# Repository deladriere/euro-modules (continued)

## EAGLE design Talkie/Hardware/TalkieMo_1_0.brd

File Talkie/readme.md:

Arduino based Talkie Eurorack Module 
Have your modular speak out the CV
This arduino based module works thanks to a clever library : Talkie from https://github.com/going-digital/Talkie 

Jean-Luc Deladrière, Hanabi SPRL 2006-2014. Except where otherwise noted, content on this site is licensed under a cc-by-sa 3.0 license.

Numbers 

#Functions
##Bank
For the moment I have added 4 sound banks :
0:digits (from 0 to 9) male voice
1:digits (from 0 to 9) female voice
2:big numbers (from 0 to 9999999)
3:voltmeter (reading the CV voltage)
4:frequencemeter (just saying "Hertz" instead of "Volts")
5:Spell the alphabet
6:nato alphabet

I plan to add a 7th bank with a large vocabulary and a 8th bank with weird sounds
random mode

##CV

CV signal change the words or phrase to be said

##Gate

Pressing the button start the complete sound in trigger mode. (regardless of it's length) 
If the trigger switch is off, the gate will start the sound and hold it as long as the gate level stays up. Very useful to create crazy rhythms.

If the cable is plugged in, the gate is triggered via an external signal

##Trigger

Choose between trigger mode or gated mode

##Bend

If bend is on, the bend pot ... distords the sound.

##Speed

Change the speed

##Pitch

Change the pitch

## Todo.todo
* publish schematic
* publish pcb
* add picture of panel & pcb
* merge library in main code 
* add R/shottky in  with entries for protection @done(2014-11-30)
* add mousers ref to each part (mouser cart : link)
* Add female voice

more info here : http://elek101.blogspot.be/2014/10/talkie-eurorack-module-part-1-concept.html

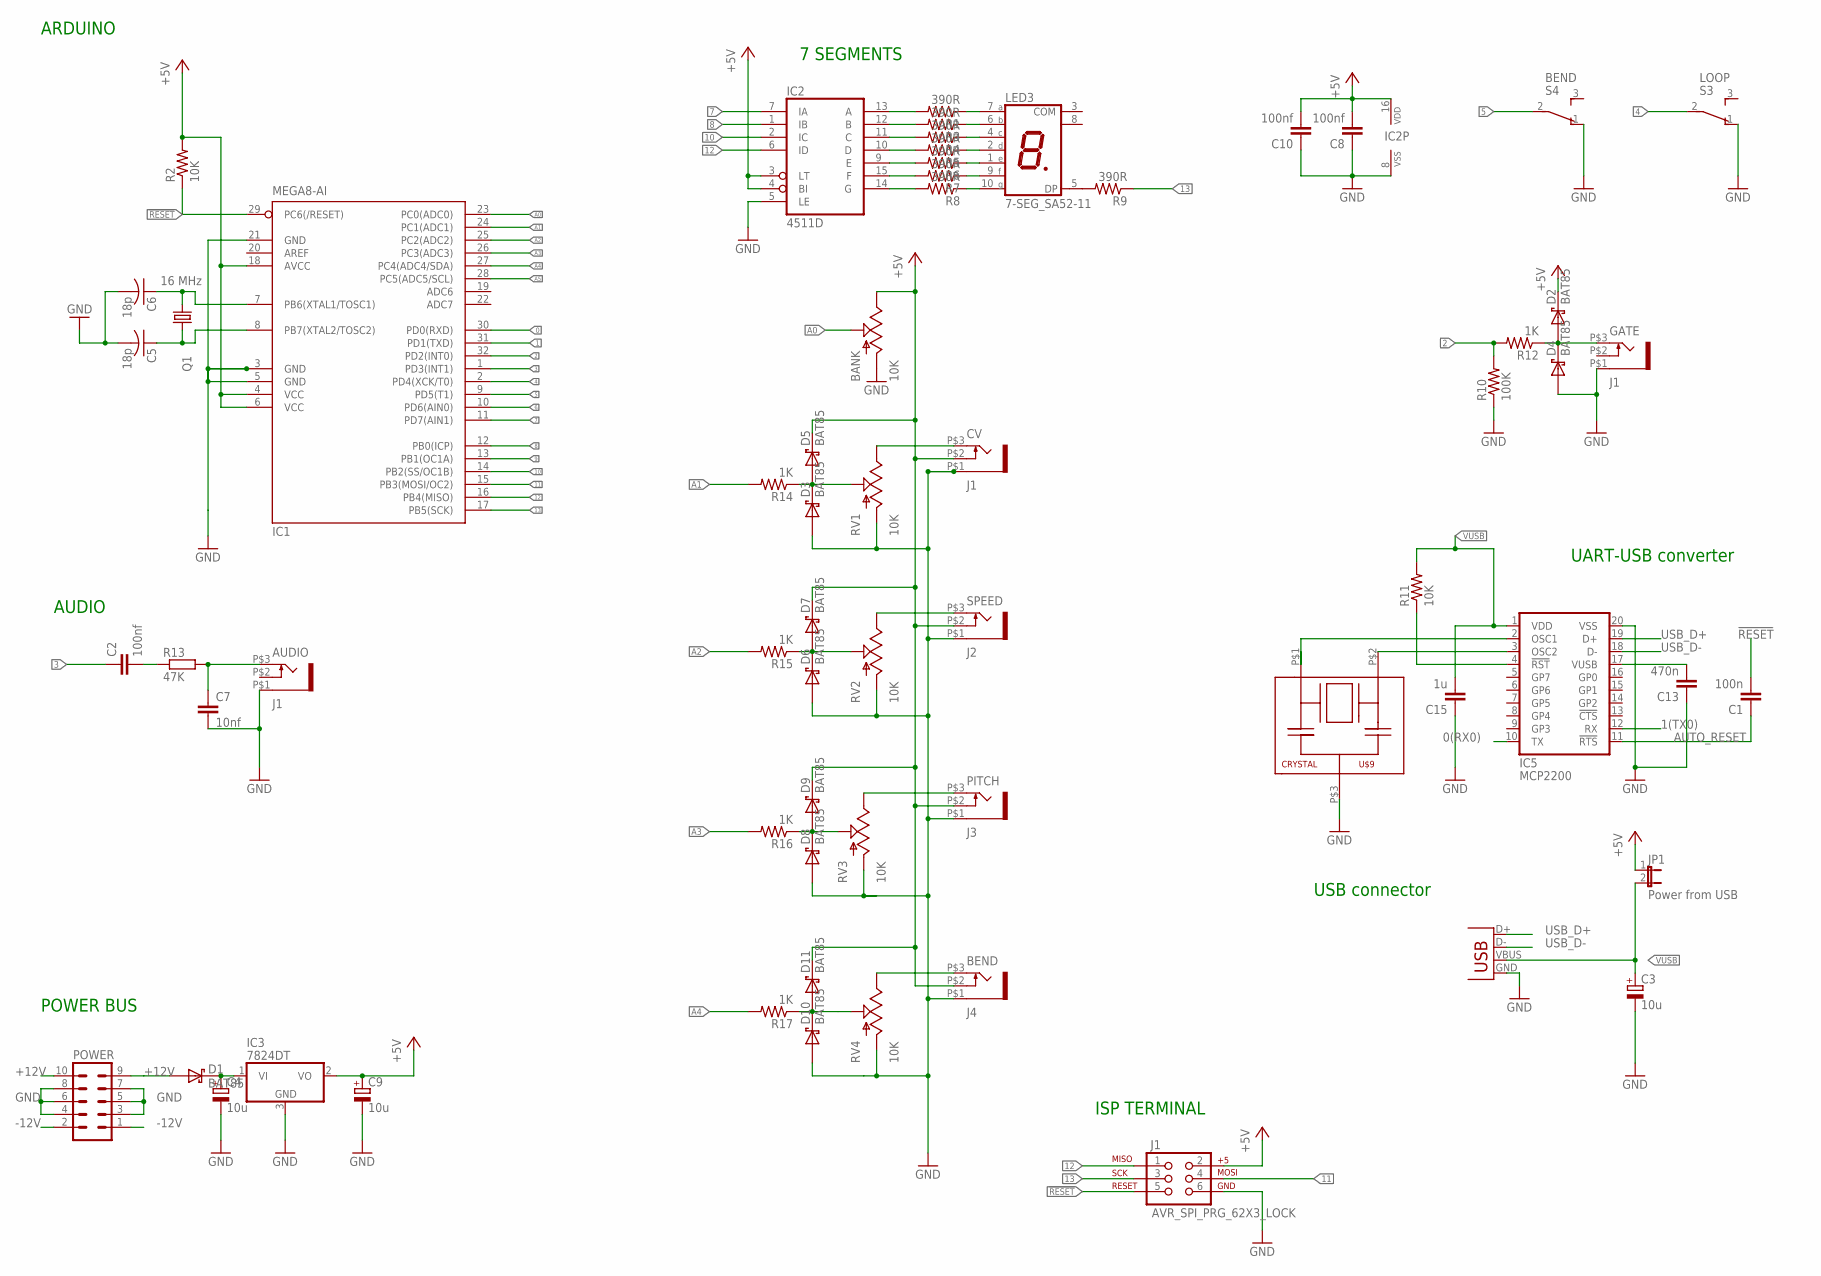
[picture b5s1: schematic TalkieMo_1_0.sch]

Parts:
AUDIO: J1; THONKICONN
BANK: 10K; ALPS_POT
BEND: J4; THONKICONN
C1: 100n; 0805
C2, C8, C10: 100nf; C0805
C3, C4, C9: 10u; R/2012-12R
C5, C6: 18p; C0805K
C7: 10nf; C0805
C13: 470n; 0805
C15: 1u; 0805
CV: J1; THONKICONN
D1, D2, D3, D4, D5, D6, D7, D8, D9, D10, D11: BAT85; SMA-DIODE
GATE: J1; THONKICONN
IC1: MEGA8-AI; TQFP32-08
IC2: 4511D; SO16
IC3: 7824DT; TO252
IC5: MCP2200; SO20
J1: AVR_SPI_PRG_62X3_LOCK; 2X3_LOCK
JP1: Power from USB; JP1
LED3: 7-SEG_SA52-11; SA52-11
PITCH: J3; THONKICONN
POWER: 10_PIN_HEADER; MA05-2
Q1: 16 MHz; CTS406
R1, R3, R4, R5, R6, R7, R8, R9: 390R; M0805
R2, R11: 10K; M0805
R10: 100K; M0805
R12, R14, R15, R16, R17: 1K; M0805
R13: 47K; M0805
RV1, RV2, RV3, RV4: 10K; ALPS_POT
S3: LOOP; TL3XPO
S4: BEND; TL3XPO
SPEED: J2; THONKICONN
U$9: CRYSTAL
X3: USB; USB-B-PTH-VERTICAL

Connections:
0: IC1.30 (PD0(RXD))
0(RX0): IC5.10 (TX)
1: IC1.31 (PD1(TXD))
1(TX0): IC5.12 (RX)
2: IC1.32 (PD2(INT0)), R10.2, R12.2
3: C2.1, IC1.1 (PD3(INT1))
4: IC1.2 (PD4(XCK/T0)), S3.2
5: IC1.9 (PD5(T1)), S4.2
6: IC1.10 (PD6(AIN0))
7: IC1.11 (PD7(AIN1)), IC2.7 (IA)
8: IC1.12 (PB0(ICP)), IC2.1 (IB)
9: IC1.13 (PB1(OC1A))
10: IC1.14 (PB2(SS/OC1B)), IC2.2 (IC)
11: IC1.15 (PB3(MOSI/OC2)), J1.4
12: IC1.16 (PB4(MISO)), IC2.6 (ID), J1.1
13: IC1.17 (PB5(SCK)), J1.3, R9.1
!RESET: C1.2, IC1.29 (PC6(/RESET)), J1.5, R2.1
+5V: BANK.P$1 (E), BEND.P$2 (4), C8.2, C9.+, C10.2, CV.P$2 (4), D2.C, D5.C, D7.C, D9.C, D11.C, IC1.4 (VCC), IC1.6 (VCC), IC1.18 (AVCC), IC2.3 (LT), IC2.4 (BI), IC2.16 (VDD), IC3.2 (VO), J1.2, JP1.1, PITCH.P$2 (4), R2.2, SPEED.P$2 (4)
+12V: D1.A, POWER.9, POWER.10
-12V: POWER.1, POWER.2
A0: BANK.P$2 (S), IC1.23 (PC0(ADC0))
A1: IC1.24 (PC1(ADC1)), R14.2
A2: IC1.25 (PC2(ADC2)), R15.2
A3: IC1.26 (PC3(ADC3)), R16.2
A4: IC1.27 (PC4(ADC4/SDA)), R17.2
A5: IC1.28 (PC5(ADC5/SCL))
AUTO_RESET: C1.1, IC5.11 (!RTS)
GND: AUDIO.P$1 (5), BANK.P$3 (A), BEND.P$1 (5), C4.-, C5.2, C6.2, C7.2, C8.1, C9.-, C10.1, C13.1, C15.1, CV.P$1 (5), D3.A, D4.A, D6.A, D8.A, D10.A, GATE.P$1 (5), IC1.3 (GND), IC1.5 (GND), IC1.21 (GND), IC2.5 (LE), IC2.8 (VSS), IC3.3 (GND), IC5.20 (VSS), J1.6, PITCH.P$1 (5), POWER.3, POWER.4, POWER.5, POWER.6, POWER.7, POWER.8, R10.1, RV1.P$3 (A), RV2.P$3 (A), RV3.P$3 (A), RV4.P$3 (A), S3.1 (O), S4.1 (O), SPEED.P$1 (5), U$9.P$3 (3), X3.GND
unnamed: CV.P$3 (3), RV1.P$1 (E)
unnamed: C5.1, IC1.8 (PB7(XTAL2/TOSC2)), Q1.1
unnamed: LED3.5 (DP), R9.2
unnamed: RV2.P$1 (E), SPEED.P$3 (3)
unnamed: C4.+, D1.C, IC3.1 (VI)
unnamed: PITCH.P$3 (3), RV3.P$1 (E)
unnamed: IC2.13 (A), R1.2
unnamed: D3.C, D5.A, R14.1, RV1.P$2 (S)
unnamed: LED3.7 (A), R1.1
unnamed: IC5.3 (OSC2), U$9.P$2 (2)
unnamed: C6.1, IC1.7 (PB6(XTAL1/TOSC1)), Q1.3 (2)
unnamed: AUDIO.P$3 (3), C7.1, R13.2
unnamed: C2.2, R13.1
unnamed: IC2.12 (B), R3.2
unnamed: LED3.6 (B), R3.1
unnamed: IC2.11 (C), R4.2
unnamed: LED3.4 (C), R4.1
unnamed: IC2.10 (D), R5.2
unnamed: LED3.2 (D), R5.1
unnamed: IC2.9 (E), R6.2
unnamed: LED3.1 (E), R6.1
unnamed: IC2.15 (F), R7.2
unnamed: LED3.9 (F), R7.1
unnamed: IC2.14 (G), R8.2
unnamed: LED3.10 (G), R8.1
unnamed: IC5.2 (OSC1), U$9.P$1 (1)
unnamed: IC5.4 (!RST), R11.1
unnamed: C13.2, IC5.17 (VUSB)
unnamed: D2.A, D4.C, GATE.P$3 (3), R12.1
unnamed: D6.C, D7.A, R15.1, RV2.P$2 (S)
unnamed: D8.C, D9.A, R16.1, RV3.P$2 (S)
unnamed: BEND.P$3 (3), RV4.P$1 (E)
unnamed: D10.C, D11.A, R17.1, RV4.P$2 (S)
USB_D+: IC5.19 (D+), X3.D+
USB_D-: IC5.18 (D-), X3.D-
VUSB: C3.+, C15.2, IC5.1 (VDD), JP1.2, R11.2, X3.VBUS

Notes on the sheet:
7 SEGMENTS
UART-USB converter
USB connector
ISP TERMINAL
POWER BUS
ARDUINO
AUDIO

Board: 2 copper layers, 64 parts (5 on the bottom side), 57 nets, no tracks yet.

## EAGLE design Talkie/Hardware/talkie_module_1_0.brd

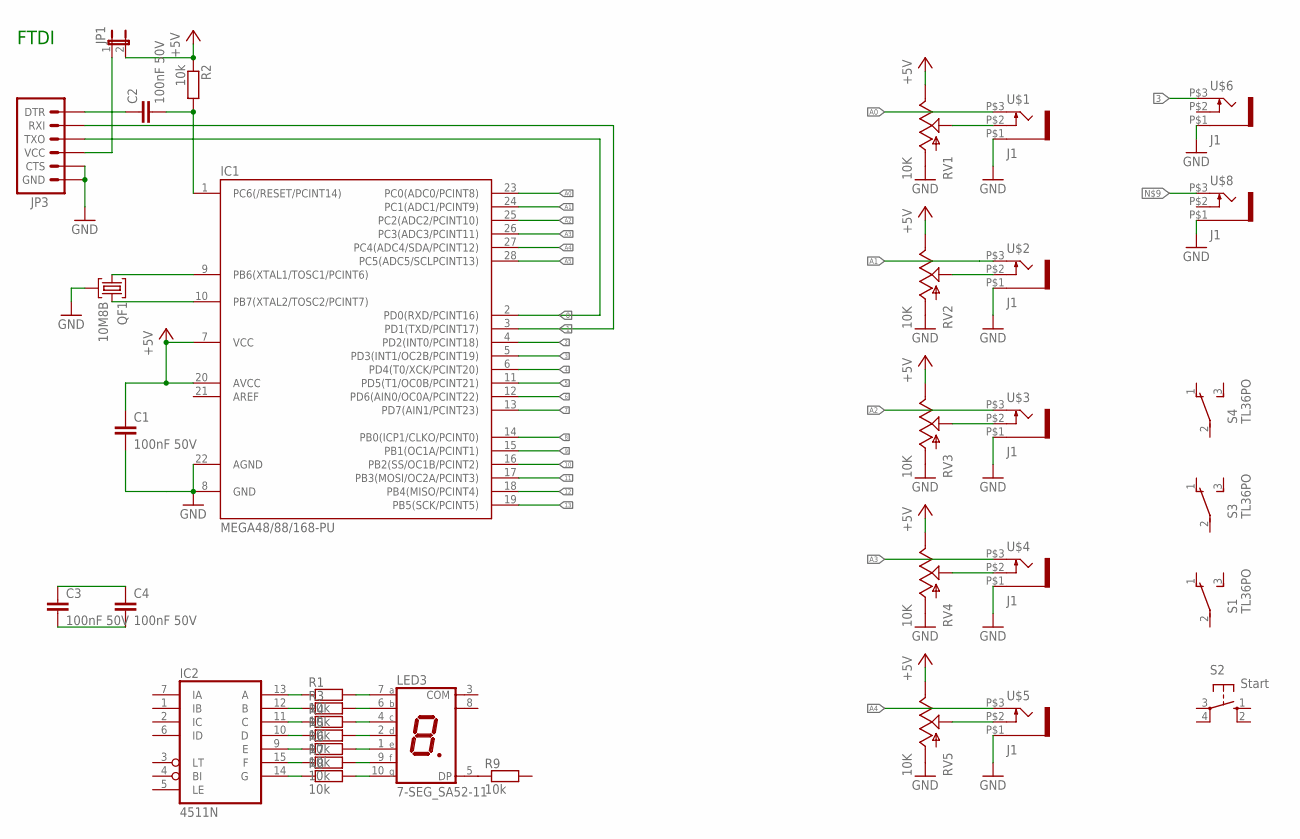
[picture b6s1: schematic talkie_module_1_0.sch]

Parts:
C1, C2, C3, C4: 100nF 50V; C025-025X050
IC1: MEGA48/88/168-PU; DIL28-3
IC2: 4511N; DIL16
JP1: JP1E; JP1
JP3: ARDUINO_SERIAL_PROGRAMLOCK; 1X06_LOCK
LED3: 7-SEG_SA52-11; SA52-11
QF1: 10M8B; HC49U
R1, R2, R3, R4, R5, R6, R7, R8, R9: 10k; RES-AXIAL-0.4
RV1, RV2, RV3, RV4, RV5: 10K; ALPS_POT
S1, S3, S4: TL36PO; TL3XPO
S2: Start; B3F-10XX
U$1, U$2, U$3, U$4, U$5, U$6, U$8: J1; THONKICONN

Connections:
0: IC1.2 (PD0(RXD/PCINT16)), JP3.3 (TXO)
1: IC1.3 (PD1(TXD/PCINT17)), JP3.2 (RXI)
2: IC1.4 (PD2(INT0/PCINT18))
3: IC1.5 (PD3(INT1/OC2B/PCINT19)), U$6.P$3 (3)
4: IC1.6 (PD4(T0/XCK/PCINT20))
5: IC1.11 (PD5(T1/OC0B/PCINT21))
6: IC1.12 (PD6(AIN0/OC0A/PCINT22))
7: IC1.13 (PD7(AIN1/PCINT23))
8: IC1.14 (PB0(ICP1/CLKO/PCINT0))
9: IC1.15 (PB1(OC1A/PCINT1))
10: IC1.16 (PB2(SS/OC1B/PCINT2))
11: IC1.17 (PB3(MOSI/OC2A/PCINT3))
12: IC1.18 (PB4(MISO/PCINT4))
13: IC1.19 (PB5(SCK/PCINT5))
+5V: C1.1, IC1.7 (VCC), IC1.20 (AVCC), JP1.2, R2.P$1 (1), RV1.P$1 (E), RV2.P$1 (E), RV3.P$1 (E), RV4.P$1 (E), RV5.P$1 (E)
A0: IC1.23 (PC0(ADC0/PCINT8)), U$1.P$3 (3)
A1: IC1.24 (PC1(ADC1/PCINT9)), U$2.P$3 (3)
A2: IC1.25 (PC2(ADC2/PCINT10)), U$3.P$3 (3)
A3: IC1.26 (PC3(ADC3/PCINT11)), U$4.P$3 (3)
A4: IC1.27 (PC4(ADC4/SDA/PCINT12)), U$5.P$3 (3)
A5: IC1.28 (PC5(ADC5/SCLPCINT13))
GND: C1.2, IC1.8 (GND), IC1.22 (AGND), JP3.5 (CTS), JP3.6 (GND), QF1.2, RV1.P$3 (A), RV2.P$3 (A), RV3.P$3 (A), RV4.P$3 (A), RV5.P$3 (A), U$1.P$1 (5), U$2.P$1 (5), U$3.P$1 (5), U$4.P$1 (5), U$5.P$1 (5), U$6.P$1 (5), U$8.P$1 (5)
unnamed: RV1.P$2 (S), U$1.P$2 (4)
unnamed: RV2.P$2 (S), U$2.P$2 (4)
unnamed: IC1.9 (PB6(XTAL1/TOSC1/PCINT6)), QF1.1
unnamed: JP1.1, JP3.4 (VCC)
unnamed: RV3.P$2 (S), U$3.P$2 (4)
unnamed: RV4.P$2 (S), U$4.P$2 (4)
unnamed: RV5.P$2 (S), U$5.P$2 (4)
unnamed: IC2.13 (A), R1.P$1 (1)
unnamed: LED3.7 (A), R1.P$2 (2)
unnamed: LED3.5 (DP), R9.P$1 (1)
unnamed: IC1.10 (PB7(XTAL2/TOSC2/PCINT7)), QF1.3
unnamed: C2.2, IC1.1 (PC6(/RESET/PCINT14)), R2.P$2 (2)
unnamed: C2.1, JP3.1 (DTR)
unnamed: IC2.12 (B), R3.P$1 (1)
unnamed: LED3.6 (B), R3.P$2 (2)
unnamed: IC2.11 (C), R4.P$1 (1)
unnamed: LED3.4 (C), R4.P$2 (2)
unnamed: IC2.10 (D), R5.P$1 (1)
unnamed: LED3.2 (D), R5.P$2 (2)
unnamed: IC2.9 (E), R6.P$1 (1)
unnamed: LED3.1 (E), R6.P$2 (2)
unnamed: IC2.15 (F), R7.P$1 (1)
unnamed: LED3.9 (F), R7.P$2 (2)
unnamed: IC2.14 (G), R8.P$1 (1)
unnamed: LED3.10 (G), R8.P$2 (2)
unnamed: C3.1, C4.1
unnamed: C3.2, C4.2
VDD: IC2.16 (VDD)
VSS: IC2.8 (VSS)

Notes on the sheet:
FTDI

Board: 2 copper layers, 35 parts (0 on the bottom side), 37 nets, no tracks yet.

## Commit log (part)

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2014-09-03 first push
2014-09-03 little update
2014-09-03 test commit
2014-09-10 pitch bending
2014-10-08 pour sauver le nouveau pcb
2014-10-08 modified readme
2014-10-08 .gitignore is now working
2014-10-08 ready to broadcast on my blog
2014-10-12 removed a redundant wait in talkie2.cpp moved definition in talkie2.h to share them across the script and talkie2.cpp change pot mapping for alphabet
2014-11-08 Explaining the little update to the original script to match the hardware
2014-11-29 MozMo opening Version 1_1 / Adding software folder
2014-12-12 Mozmo software update Talkie added female voice Talkie rename pcb
2014-12-30 Talkie renamed to Talko Talko Schematic Added female voice
2014-12-30 updating Talko readme
2015-01-03 adding schematic image file to Talko
2015-01-17 renaming mozzi folder to mozmo
2015-01-20 Fixing a bug in loop mode changing switch reference @ Mouser (for a bigger lever)
2015-01-28 Adding jumper picture to Mozmo Adding vocabulary to Talko Adding Counter mode to Talko Use dot led for mode > 10
2015-01-28 Changing Mozmo Jumper picture to png
2015-02-27 adding turing machine script to Mozmo
2015-03-08 Adding a LFO for MozMo
2015-03-18 Minor changes to MozMo's LFO
2015-03-18 Adding noise color option to noise generator
2015-03-19 changing Mozmo image in readme
2015-03-25 First Raspo commit : eagle schematic & numbers radio simulator
2015-03-25 adding talko images
2015-03-25 adding Talko pcb image
2015-03-29 Adding pcb image error 1
2015-03-29 Adding error on Talko's pcb
2015-03-29 Posting Talko's panel (still drafted)
2015-04-13 Updating Mozmo readme
2015-04-17 adding link to Mozmo's install page
2015-04-17 update Talko's readme
2015-05-27 Adding a basic setup schematic
2015-05-27 Updated basic drawing
2015-05-29 Updated pcb to version 1.1 Updated Readme to explain changes
2015-07-08 renaming Talko pots on v1.1
2015-07-18 Adding panel to Talko New version of Talko_1 : added 60 words and random words mode
2015-07-19 Adding Talko panel image
2015-07-29 Update Talko pot Pitch & Speed position Added more words to vocabulary (now has 60)
2015-07-29 Uploading Talko assembly pictures
2015-07-29 Resize Talko panel image
2015-07-31 Talko readme update
2015-08-07 removing morse
2015-08-07 Updating Talko's readme
2015-08-08 Fixing Talko code under Arduino 1.6.x Adding link to Talko uploading code
2015-08-26 adding Bank # 12 : DSC sentences
2015-09-19 Uploading Cantarino example for Talko
2015-09-22 Adding Canto script to Talko
2015-09-27 Uploading Talko_QC
2015-09-27 Talko switch back to low = active
2015-10-07 Various updates on Mozmo & Talko
2015-10-07 Canto new version : Gate trigger : vowel holds while gate is on - use duty cycle of gate to give rhythm (I use my LFO2 from Pittsburg Modular for that) Sound : choose between 19 different vowels soun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
2015-10-07 Updating Readme because it works fine on all OS
2015-10-11 Taco's Canto has now pitch bend and sound change while note one
2015-12-04 Talko : updating bending intensity to a stronger effect Adding interupt to change bank when gate is rising Moving Readme to http://www.polaxis.be/talko/
2015-12-13 Talk update : reverse speech/loop switch position : lever down for loop mode
2015-12-26 Talko : made some room to prepare for French digit / Talko_QC added interrupt change to blink LED 13 on gate
2015-12-28 Talk : Adding a new sentence coded with QBoxPro
2016-01-08 renaming Talko_1 to Talko + adding a zip to hold these 3 files :-)
2016-01-15 Pushing TalkoVCO for the first time
2016-02-05 TalkoVCO testing "mouth drum"
2016-03-04 Talk new version of VCO : includes now a "Throat Beat Box" mode
2016-03-24 VCO mode : adding 2 new words "Error" "Instruments"
2016-03-24 Adding TalkoVCO Zip file
2016-04-13 Adding code for Talko 1.2
2016-04-27 Talk 1.2 includes VCO mode
2016-05-18 adding images to talko manual
2016-05-18 Adding picture to Talko 1.2 assembly manual
2016-05-18 Adding images to Talko 1.2 Assembly Manual
2016-05-18 Updating image
2016-07-27 Adding some Grains code to talko
2016-07-27 Delete .DS_Store
    deletion od .ds_store
2016-08-23 Talko : Changed #include<Time.h> into #include<Timelib.h> (compilation issues)
2016-11-16 Adding Aques click board
2016-11-23 adding SAMD21 code
2016-11-23 Kaija vox : main functions working
2016-11-23 Emy first commit
2016-11-25 minor update on Emy ! hang on exit from SD tts
2016-11-30 Adding Hataken’s timer
2016-11-30 Correction on vocal countdown for Hataken’s timer
2016-11-30 Adding code to Emy platform
2016-11-30 Kaiwa dirty fixing Interrupt trigger when using rotary even if if interrupt is detached !!!
2016-12-14 Hataken’s timer : connected to Processing
2016-12-14 Kaiwa now connected to Kaiwa VOX and speaking
2016-12-17 Kawai : removing interrupt triggering of voice + extended I2C message to 50 bytes (instead of 32 !)
2016-12-17 kaiwa : testing priority to gate (not very fast :-( )
2016-12-18 Updating Talko Hardware with version 1.2 (sorry I should have done that long time ago)
2016-12-21 Adding switches in emy QC
2016-12-21 Kaiwa sending the correct String lenght to synth
2016-12-21 various trivial changes
2016-12-31 Kaiwa speaks from SD
2017-01-06 Kaiwa : display SD error + voice parameter while SD card reading
2017-01-11 Adding Talko1.2 midi
2017-01-11 Talko midi : need to read midi while looping in vco . will this work ? ….
2017-01-11 Kaiwa : get correct line when gate goes high
2017-01-20 adding Talko Print notes
2017-01-21 Mea Vox first commit
2017-01-21 Kaiwa Vox first commit
2017-01-30 Mea_Vox_Arduino simplify connections
2017-02-01 trying to install my own board management
2017-02-01 Testing custom board management
2017-02-03 Kaiwa : first test for long vowels
2017-02-15 Kaiwa : master clock hack while sd tts
2017-02-18 Updates to Talko Readme
2017-02-22 Talko VCO mode uses 1V/octave tracking to play notes.
2017-03-01 Kaiwa : move master pitch function in main menu
2017-03-04 Talko Box : new iteration
2017-03-04 Talko Box : addling Minitel connector
2017-03-04 Talko Box : full with midi connector
2017-03-08 Emy : testing Adafruit library
2017-03-22 Kaiwa : long press to get out from master clock & short press to change pitch
2017-03-22 Emy: the story begin
2017-03-22 Talko : small tweak to 3D box
2017-03-22 Talko : updating readme
2017-03-23 Kaiwa: master tune value from rotary
2017-03-29 Kaiwa : reset font after master Tune changed
2017-05-08 EMY 1_0 : responsive read pots / Gate interrupts for LED
2017-05-12 Emy QC : adding analog correction
2017-05-12 Emy 1.0 : Trying to add speed mode + trigger mode
2017-05-13 Emy 1.0 : Adding Rate pot
2017-05-15 Emy 1.0 : Adding Menu
2017-05-18 Talko : Adding fuses setup and Optiboot
2017-05-26 Emy : Repeat mode ok
2017-05-26 Emy Repeat / speech ok for Phoneme
2017-05-26 Emy : listing files ok
2017-05-26 Emy: reading chosen file
2017-05-26 Emy : reading label name from SD card
2017-05-26 Emy: Storing data stream in variable
2017-05-31 Emy 1.0: Speaking from SD (^_^)
2017-06-09 Emy 1_0: Change timing value for rate & stretch
2017-06-17 Emy 1_0: I2C clock to 2.5 MHZ seems optimum / adding busy(ready) signal
2017-06-17 Emy 1_0: Growling mode ok
2017-06-24 EmyLoader : first commit
2017-06-24 EmyLoader : adding console area
2017-06-30 EmyLoader : problem compiling with "orbitron.ttf" / need to check how to use font
2017-06-30 Emy: adding bending pot
2017-06-30 Emy:Moving reading sd root into functions to prepare for file type
2017-06-30 Emy: list file according their extensions
2017-07-15 moving Emy into dedicaded repository
2017-10-15 Delete Talko_1_0.html
    deleting
2017-10-15 removing Eagle board files
2017-10-15 Clean the board files
2017-10-15 removing some files
2017-10-15 cleaning up files ...
2017-12-26 Adding Bossa Loader v1.0
2018-01-31 MeaVox : adding the RTC talking clock (in french)
2018-02-12 Adding Serial terminal
2018-02-13 Vax : adding Vax 1.0
2018-02-13 VAX : moving setup near loop
2018-02-25 Vax SD & Speech working together !
2018-04-21 Bossaloader update
2018-06-09 VAX : first test reading sd card
2018-06-09 VAX: saving
2018-06-09 VAX : restart mode
2018-06-27 Vax: now reading files with indexes
2018-09-07 Vax : improved long press detection / display voice names / improved test display for long sentence
2019-03-06 Mea_vox Parole first commit
2019-03-06 Mea Vox Using PROGMEM for allophones
2019-03-06 Mea Vox : spell & find works
2019-03-09 Mea vox : adding text to speech
2019-05-25 adding Robo vox code
2019-05-29 Robovox Arduino : now using LTC6903 as clock
2019-06-05 just saving the CTL bit sequence
2019-06-05 adding LTC6903 clock for midi
2019-06-07 adding Robovox Emy
2019-06-14 Adding SDU to Robovox for Emy
2019-06-19 adding Robovox for MIDI
2019-06-22 Robovox Emy MIDI : mapping the original Robovox from Kraftwerk / display note being uttered
2019-06-23 Robovox Midi Emy : toggling the Busy signal to measure latency
2019-07-05 improved note latency / Pitch on channel 2 (just pitch no notes yet)
2019-07-06 Robovox MIDI : adding Pitchwheel for clock control and Modwheel for filter
2019-07-13 Adding platformio.ini
2019-10-06 Adding MEA8000 Minitel interface
2019-12-06 Adding processing Alva Noto style processing
2019-12-09 removing processing folder
2020-02-08 Adding Robovox_emy_midi_tiny
2020-02-12 Robovox : adding external source control with SW1
2020-02-12 Robovox ; now showing up as "Robovox" ;-)
2020-02-19 Robovox : sending phoneme label via serial / "hello world" on internal carrier
2020-03-04 Robovox : adding the option to disable the display
2020-03-21 Adding Mouth for Robovox
2020-03-21 oops I forgot the folder for Mouth2D
2020-03-21 remove the svg mouth
2020-03-21 Robovox MIDI USB : Update via SD card, External carrier via CC sustain or front panel switch (mid-low position)
2020-03-23 Robovox Midi USB : uploading missing files
2020-03-29 Applies hack to silence carrier noise in external carrier mode.
2020-04-05 Adding knob control of SC02 parameters
2020-04-08 Robovox MIDI USB : Added MIDI channel chooser via the rotary knob / see readme for more
2020-04-09 Adds phonem randomization on P5, and CV triggering with GATE of SOUND-selected phonem
2020-04-12 Robovox : added a #define to choose between USB or Serial MIDI
2020-07-18 Robovox testing inflection via MIDI
2020-07-18 Robovox v.0.5 Pitch control with CC2
2020-07-24 Robovox : updating firmware version to 0.06
2020-09-23 Fork Robovox to simplify MIDI libraries
2020-09-23 Adding Sinovox first commit
2020-09-30 Sinovox : adding main menu
2020-10-04 Sinovox : added reset control and running now at 115200 bauds. First test with numbers
2020-12-20 Sinvox : adding English / Chinese pot to number function
2020-12-20 VoxiPi : adding Mea and Sino example (in Processing)
2020-12-31 sinovox : adding usb terminal mode
2021-01-10 Sino Vox : adding a file reader from the micro SD card (character mode)
2021-01-16 Sinovox reader saving status
2021-01-23 SinoVox : can choose a marker to trigger the speech (character/space/newline). P5 to choose between spell or word mode
2021-01-30 Sinovox : SD reader now looping / Exit on long press working / Display string on oled while speaking
2021-02-03 Sino Vox : added calibration mode
2021-02-13 Sinvox 0.21 minor fixes
2021-02-24 Robovox : adding CC 3 for speech rate
2021-03-20 SinoVox Adding Midi mode
2021-03-20 Sinovox : adding custom USB name
2021-03-21 SinoVox 0.22 added Skipping Word mode
2021-03-27 Sino : rename custom_hwids.py
2021-06-09 clean up
2021-08-11 Adding Speakjet
2021-08-25 Speakjet: first tentative for tempo sync on gate
2021-09-12 Speakjet : adding priority to phoneme duration and (tentative) avoid buffer overfill
2021-09-26 Radio vox fm first commit
2021-09-27 Radio vox : adding RSSi Vu meter
2021-10-07 RadioFM saving progress
2021-10-09 Radio vox fm : fixing stuff
2021-10-13 FM Radio vox : adding main menu
2021-10-16 Radio vox : saving status
2021-10-17 radio remove files
2021-10-17 kaiwa : remove sch
2021-10-17 mea : remove sch
2021-10-19 Radio FM : storing favorite frequencies on the microSD card
2021-10-21 Radio FM: version 1.0
2021-10-26 Radio vox FM : display frequency changed for tens, units & decimals
2021-11-09 Radio FM : updating the screen saver
2021-11-23 Sinovox 0.3 : adding a screen saver
2021-12-20 Cleaning up
